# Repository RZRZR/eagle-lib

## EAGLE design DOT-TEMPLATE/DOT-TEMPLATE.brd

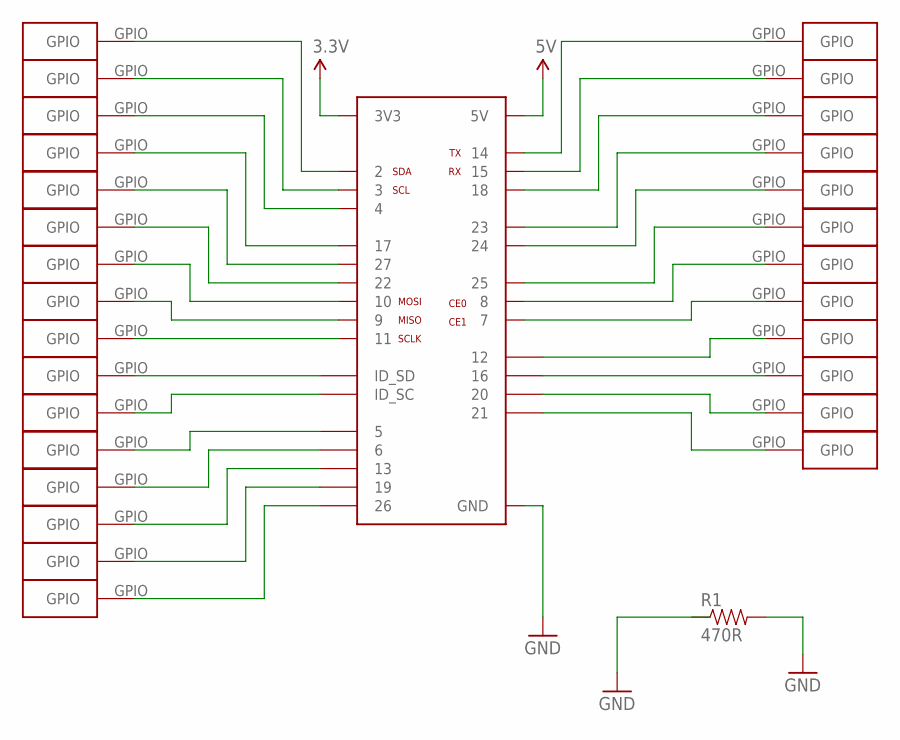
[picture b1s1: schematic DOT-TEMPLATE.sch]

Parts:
AIR, AIR1, AIR2, AIR3, AIR4, AIR5, AIR6, AIR7, AIR8, AIR9, AIR10, AIR11, AIR12, AIR13, AIR14, AIR15, AIR16, AIR17, AIR18, AIR19, AIR20, AIR21, AIR22, AIR23, AIR24, AIR25, AIR26, AIR27: DOT; DOTPAD
R1: 470R; 0603-RES
U$1: RPIGPIOPINHD-2X20-SMD-FLIPPED; FCI_89898_313LF_40P_CONNECTOR_SMT_FLIPPED

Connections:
3.3V: U$1.P1_3V3 (3V3), U$1.P17_3V3 (3V3)
5V: U$1.P2_5V (5V), U$1.P4_5V (5V)
GND: R1.2, U$1.P6_GND (GND), U$1.P9_GND (GND), U$1.P14_GND (GND), U$1.P20_GND (GND), U$1.P25_GND (GND), U$1.P30_GND (GND), U$1.P34_GND (GND), U$1.P39_GND (GND)
unnamed: AIR10.GPIO, U$1.P3_GPIO2_SDA (2)
unnamed: AIR9.GPIO, U$1.P5_GPIO3_SCL (3)
unnamed: AIR.GPIO, U$1.P7_GPIO4 (4)
unnamed: AIR1.GPIO, U$1.P11_GPIO17 (17)
unnamed: AIR2.GPIO, U$1.P13_GPIO27 (27)
unnamed: AIR3.GPIO, U$1.P15_GPIO22 (22)
unnamed: AIR4.GPIO, U$1.P19_GPIO10_SPI0_MOSI (10)
unnamed: AIR5.GPIO, U$1.P21_GPIO9_SPI0_MISO (9)
unnamed: AIR6.GPIO, U$1.P23_GPIO11_SPI0_SCLK (11)
unnamed: AIR7.GPIO, U$1.P27_IDSD (ID_SD)
unnamed: AIR8.GPIO, U$1.P28_IDSC (ID_SC)
unnamed: AIR11.GPIO, U$1.P29_GPIO5 (5)
unnamed: AIR12.GPIO, U$1.P31_GPIO6 (6)
unnamed: AIR13.GPIO, U$1.P33_GPIO13 (13)
unnamed: AIR14.GPIO, U$1.P35_GPIO19 (19)
unnamed: AIR18.GPIO, U$1.P8_GPIO14_UART0_TXD (14)
unnamed: AIR15.GPIO, U$1.P37_GPIO26 (26)
unnamed: AIR16.GPIO, U$1.P10_GPIO15_UART0_RXD (15)
unnamed: AIR17.GPIO, U$1.P12_GPIO18 (18)
unnamed: AIR19.GPIO, U$1.P16_GPIO23 (23)
unnamed: AIR20.GPIO, U$1.P18_GPIO24 (24)
unnamed: AIR21.GPIO, U$1.P22_GPIO25 (25)
unnamed: AIR22.GPIO, U$1.P24_GPIO8_SPI0_CE0 (8)
unnamed: AIR23.GPIO, U$1.P26_GPIO7_SPI0_CE1 (7)
unnamed: AIR24.GPIO, U$1.P32_GPIO12 (12)
unnamed: AIR25.GPIO, U$1.P36_GPIO16 (16)
unnamed: AIR26.GPIO, U$1.P38_GPIO20 (20)
unnamed: AIR27.GPIO, U$1.P40_GPIO21 (21)

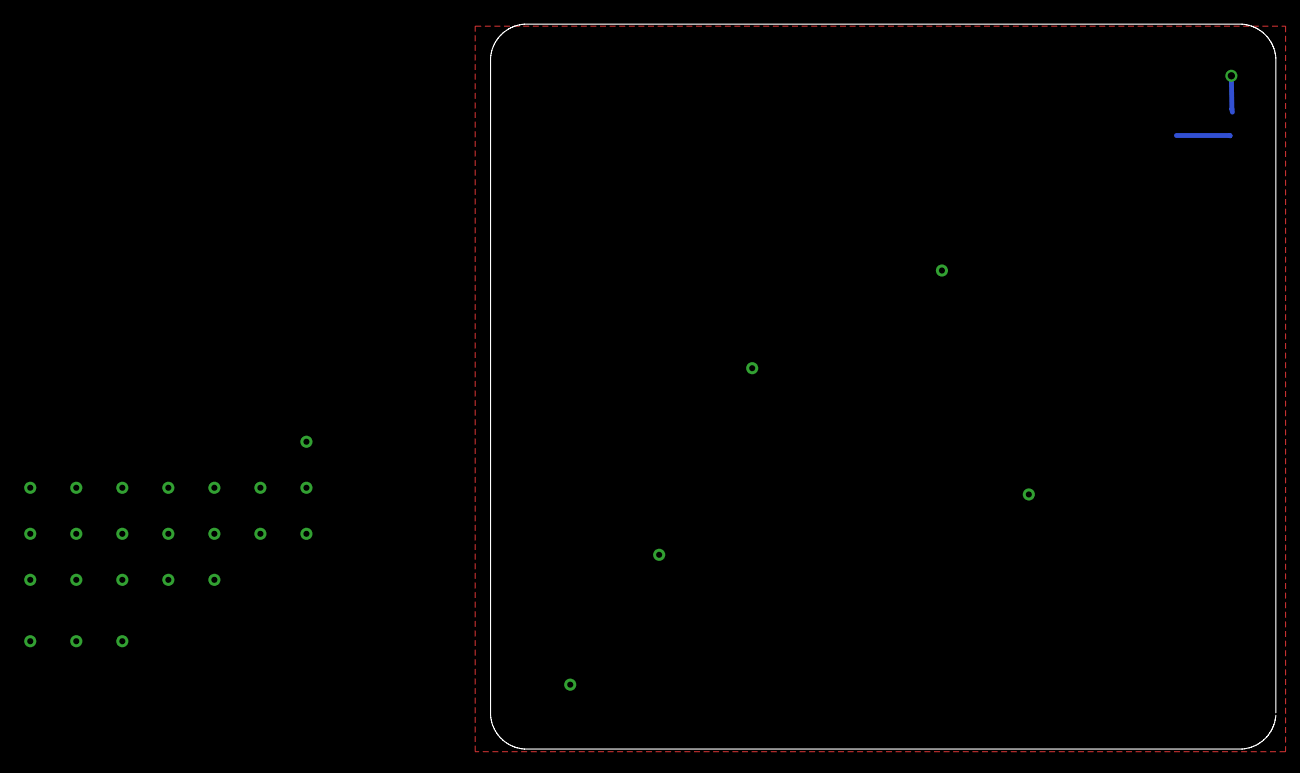
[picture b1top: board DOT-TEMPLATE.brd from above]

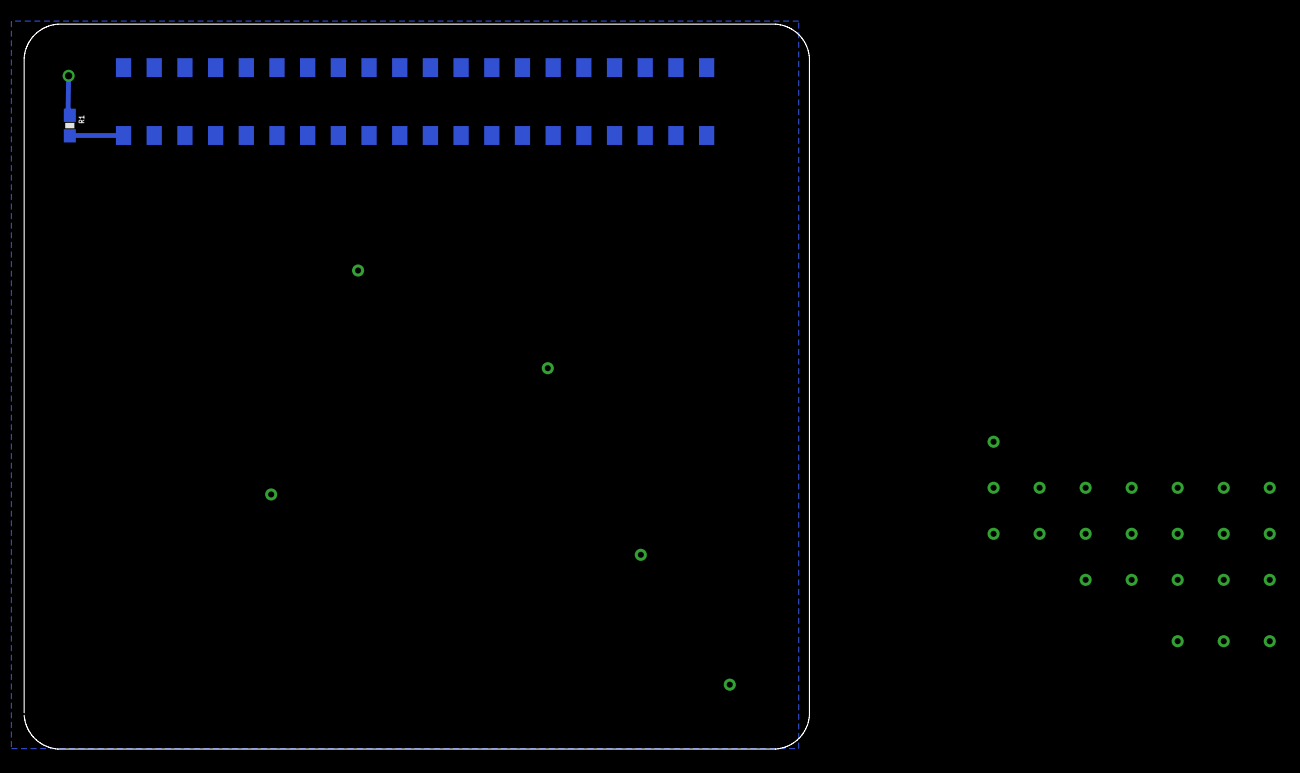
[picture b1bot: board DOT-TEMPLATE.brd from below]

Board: 2 copper layers, 65.0 x 60.0 mm, 30 parts (2 on the bottom side), 31 nets.

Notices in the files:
parts and their libraries:
SparkFun-Passives: Licensing: Creative Commons ShareAlike 4.0 International - https://creativecommons.org/licenses/by-sa/4.0
pimoroni: Licensing: CC v3.0 Share-Alike You are welcome to use this library for commercial purposes.
